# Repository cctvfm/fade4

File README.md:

# fade4
A performance MIDI and CV controller based on SAMD21G

Fade 4 runs on an Atmel SAMD21G microcontroller running the Feather M0 Bootloader. This allows Fade 4 to be developed on using the Arduino programming environment, and make use of Arduino libraries.

The SAMD21G handles all USB communication while using it's internal ADCs to read the positions of the faders. Each fader is connected between 0V and 3.3V, with the wiper providing a voltage between 0V and 3.3V. An opamp is used to multiply this voltage by 1.5x to provide 0 to 5V to the CV outputs. The fader position is sampled through Responsive Analog Read to smooth out any jumpiness in the measurement.

MIDI is handled using the Forty Seven Effects MIDI Library, making sending MIDI and USB MIDI the simplest part of this device.

The 7 segment LED displays are of the common cathode type, meaning the 7 LEDs in the character have their anodes broken out to individual pins, while the cathodes are grouped together into one pin. I use a 2N3904 transistor connected to this cathode pin to enable the digit, allowing the 4 digits to share character pins, as long as each has its own transistor and cathode pin. 

These displays need to be enabled one at a time, and using persistence of vision it appears that the 4 digits are on all the time. The timing of these characters is handled by TC3, triggering an interrupt to turn the current LED charactor off, reconfigure the pins, and turn the next one on.

A second timer, TC0, is used to generate a PWM signal on the 4 cathode transistor pins. This PWM signal can be changed to adjust the brightness of the display from 0 to 100%.

_FIRMWARE UPDATE_

1) Download the .UF2 file for the new firmware

2) Remove the 4 screws on the bottom of Fade 4, and remove the cover.

3) Plug Fade 4 into your computer using  a USB-C cable. Mac or Windows or Linux, doesn't matter. It will show up as a MIDI device named "Fade 4".

4) Double tap the button on the PCB marked "RESET". Two quick presses. A USB drive will appear on your computer, labelled "FEATHER" or "FEATHERBOOT"

5) Copy and paste the UF2 file into the USB drive. If prompted to overwrite, select YES.

6) Unplug, and reinstall the bottom cover. The firmware has been updated.

_HACKING_

You just need the .ino file in a folder named the same as it. Arduino or Arduino IDE, but you will need the following packages:

Adafruit SAMD Board Package
Flash Storage
Responsive Analog Read
MIDI

All firmware updates can be done over the USB C port. The 4 pin header is just for initial bootloader burn using an SWD programmer.

*November 2023:* 5 units built for testing. These are V1.0 units. They have an issue where the ADC is referenced to 5V and not 3.3V, so depending on USB power supply, the faders may not reach all the way to 127. fade4.ino.feather_m0-MAX975.uf2 provided as a fix for these units.

*April 15 2024:* Initial kit run. V1.1 released, fixes above issue. Build guide published to cctv.fm/fade4. Shipped with V1.1 preflashed.

*April 17 2023:* Bug fix, channels via TRS do not match channels via USB. Due to USB library counting channels from 0 and MIDI library counting from 1.

*May 8 2024:* Chris found a bug causing Program Changes to not function at all on V12, added bounds checking to message types.

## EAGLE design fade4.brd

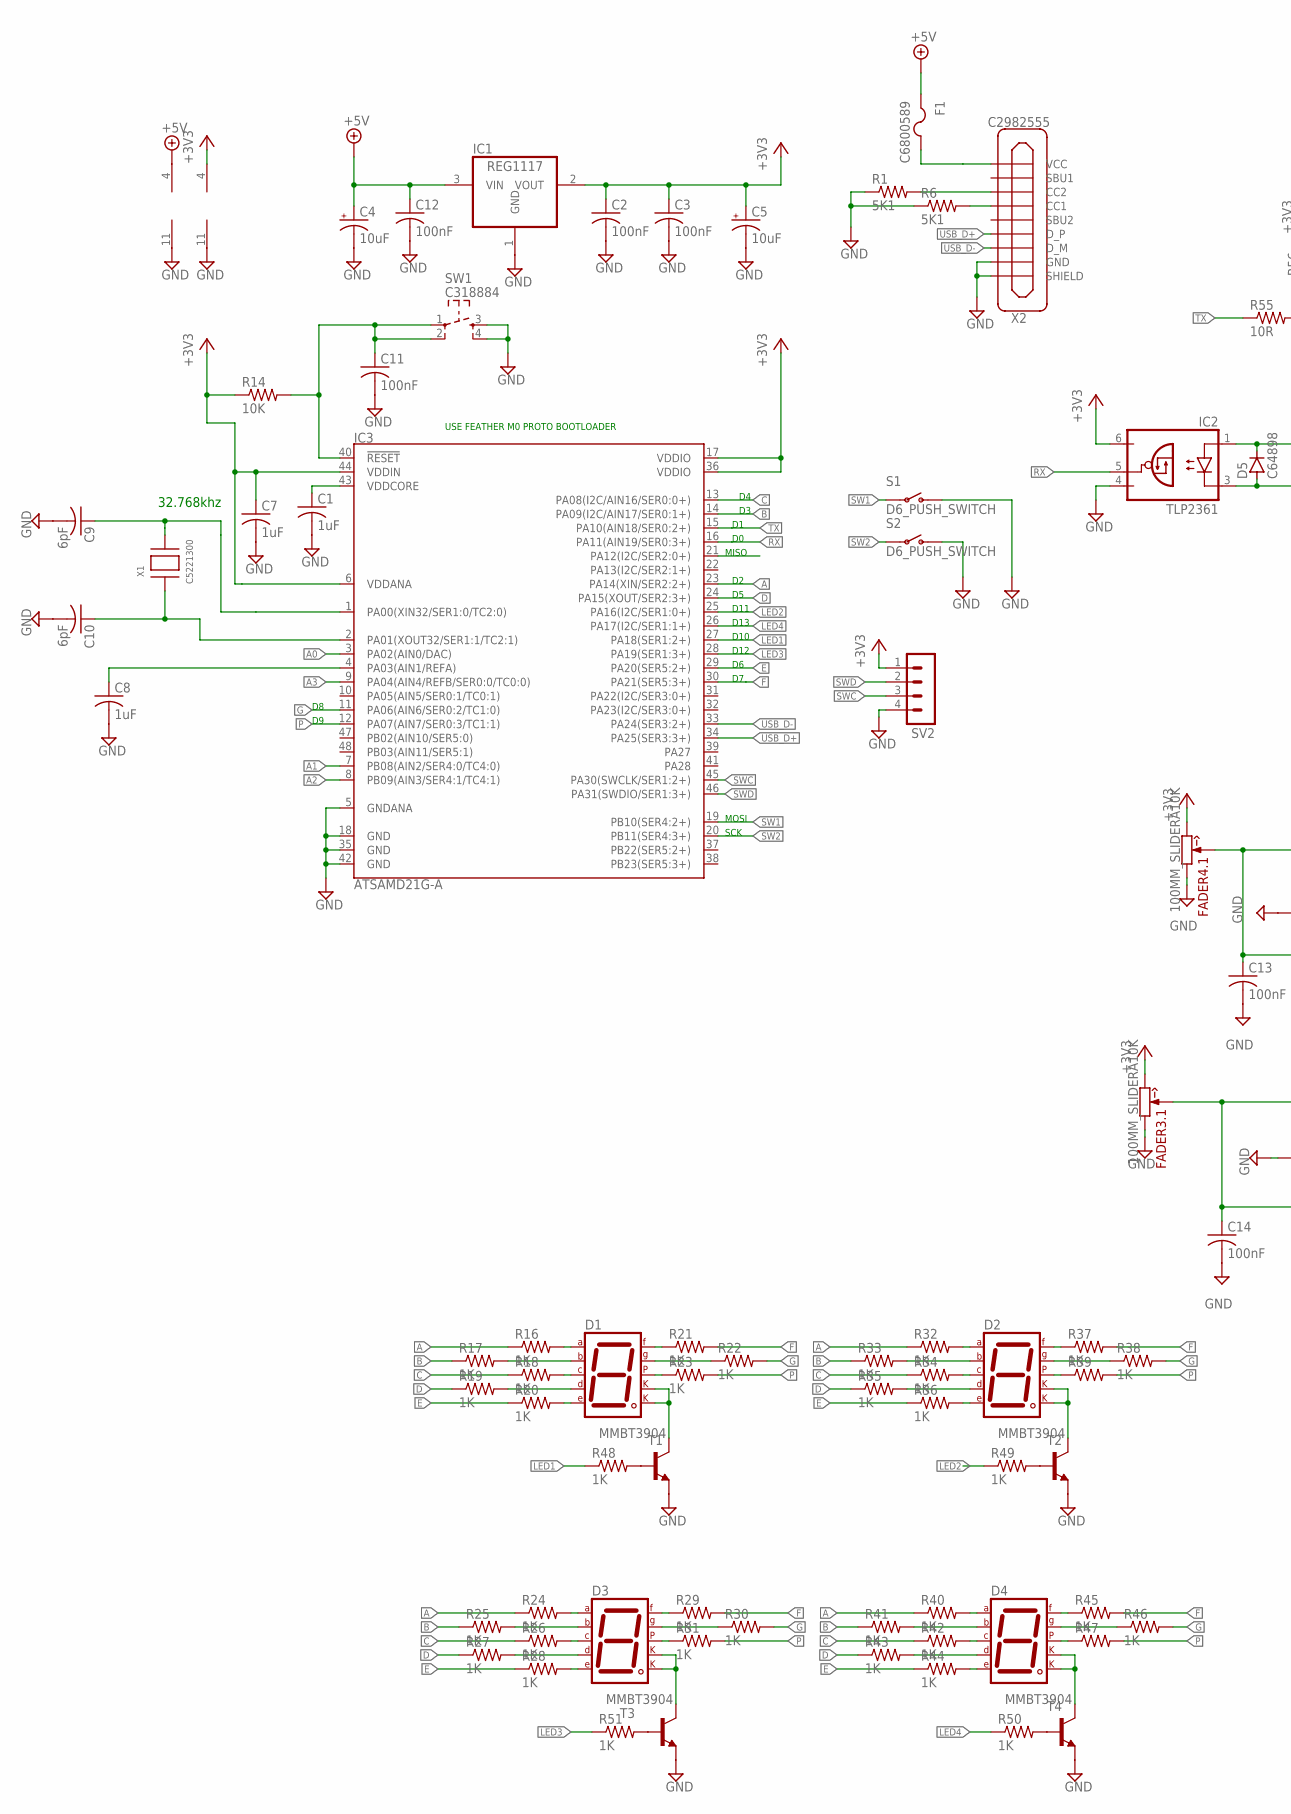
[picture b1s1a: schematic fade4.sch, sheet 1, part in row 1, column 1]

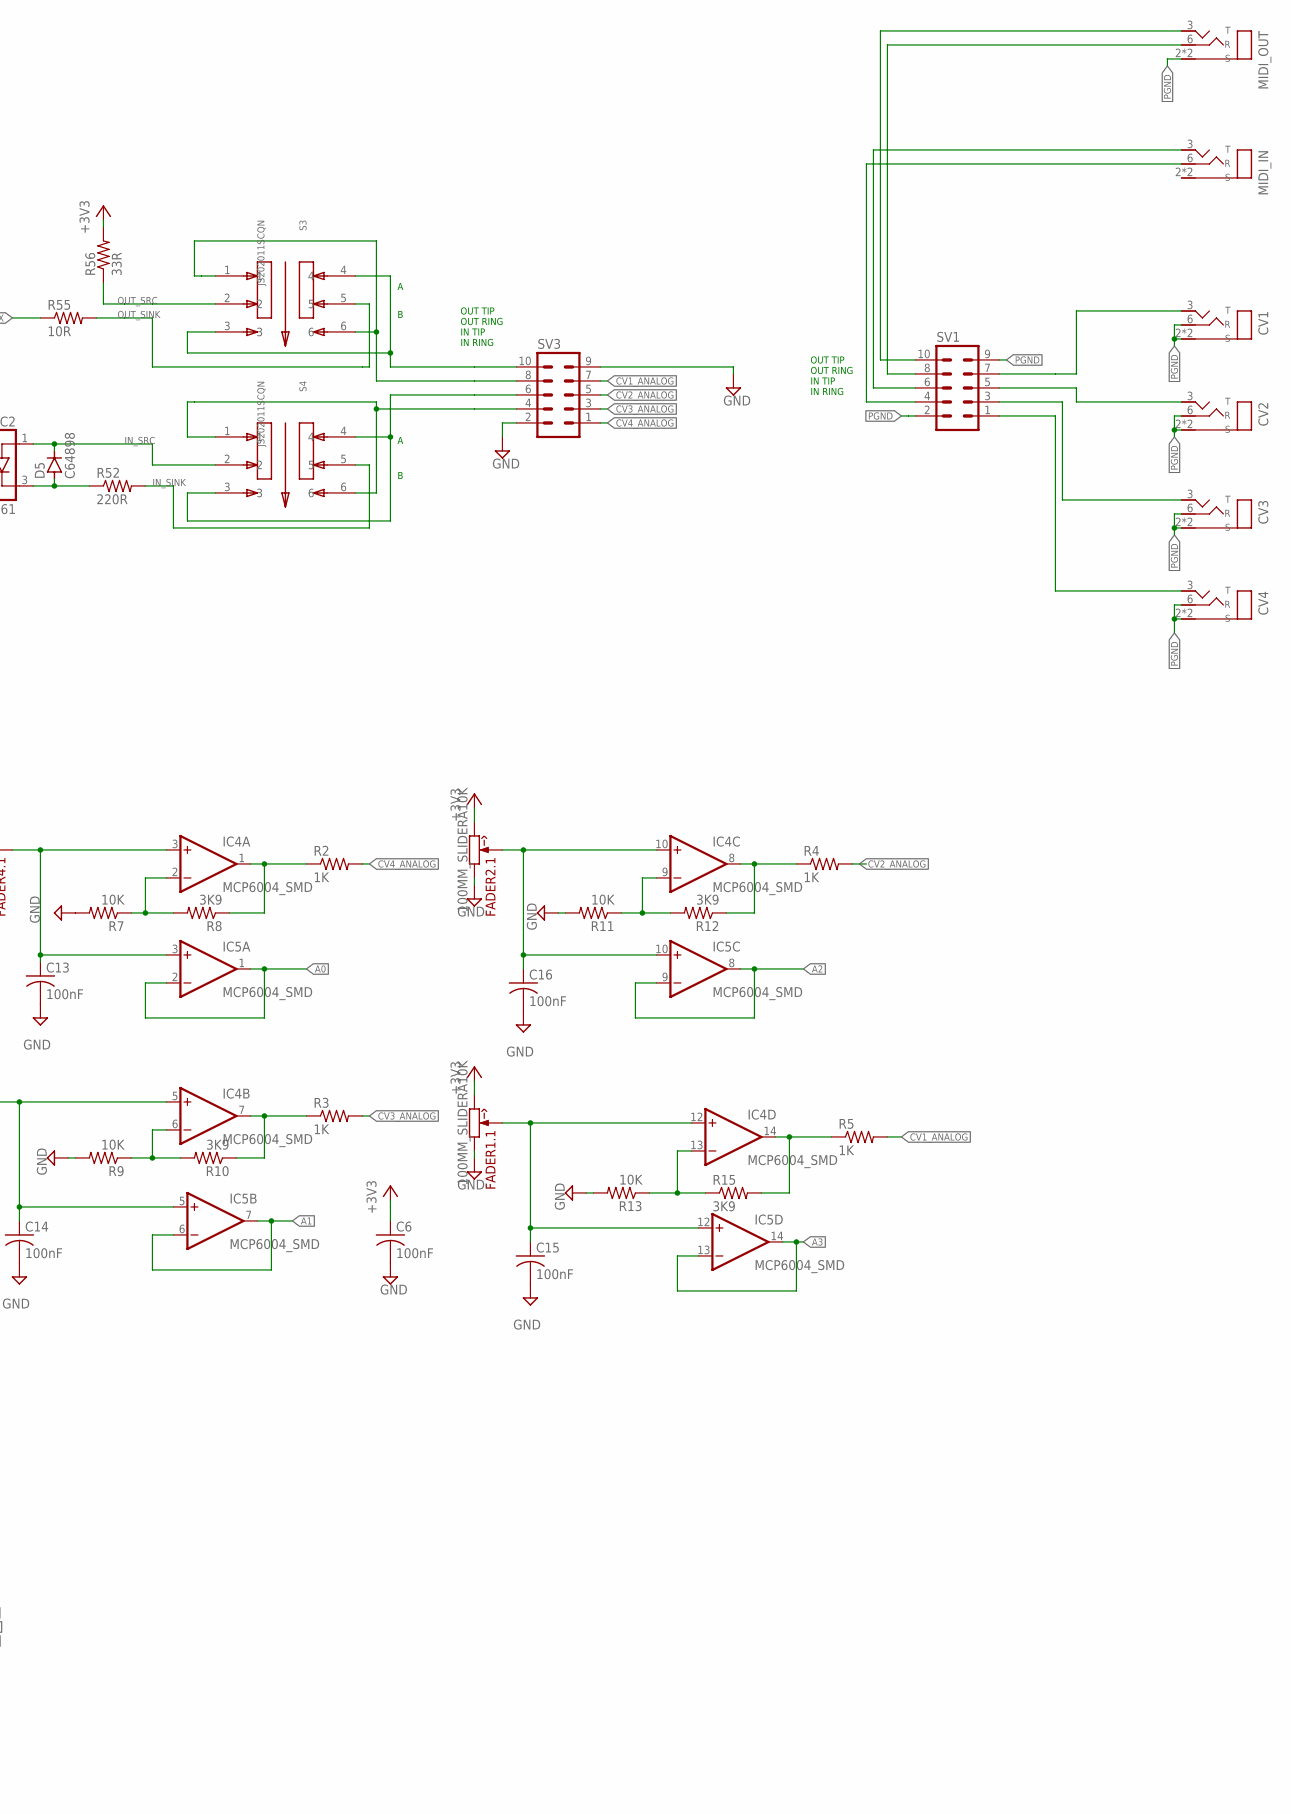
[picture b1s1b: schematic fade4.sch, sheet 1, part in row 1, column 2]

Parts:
C1, C7, C8: 1uF; C0603K
C2, C3, C6, C11, C12, C13, C14, C15, C16: 100nF; C0603K
C4, C5: 10uF; A/3216-18R
C9, C10: 6pF; C0603K
CV1, CV2, CV3, CV4: C725772
D1, D2, D3, D4: 7SEG-CK; 7SEG-13
D5: C64898; SOD123
F1: C6800589; R1206
FADER1, FADER2, FADER3, FADER4: 100MM_SLIDERA10K; 100MM-SLIDER
IC1: REG1117; SOT223
IC2: TLP2361; SOIC-5
IC3: ATSAMD21G-A; TQFP-48
IC4, IC5: MCP6004_SMD; SO14
MIDI_IN: C725772
MIDI_OUT: C725772
R1, R6: 5K1; R0603
R2, R3, R4, R5, R16, R17, R18, R19, R20, R21, R22, R23, R24, R25, R26, R27, R28, R29, R30, R31, R32, R33, R34, R35, R36, R37, R38, R39, R40, R41, R42, R43, R44, R45, R46, R47, R48, R49, R50, R51: 1K; R0603
R7, R9, R11, R13, R14: 10K; R0603
R8, R10, R12, R15: 3K9; R0603
R52: 220R; R0603
R55: 10R; R1206
R56: 33R; R1206
S1, S2: D6_PUSH_SWITCH
S3, S4: JS202011SCQN; SW_JS202011SCQN
SV1, SV3: MA05-2
SV2: MA04-1
SW1: C318884; SW_TACT_SMALL
T1, T2, T3, T4: MMBT3904; SOT23-BEC
X1: C5221300; XTAL3215
X2: C2982555

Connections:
+3V3: C2.1, C3.1, C5.+, C6.1, C7.1, FADER1.A3 (CW), FADER2.A3 (CW), FADER3.A3 (CW), FADER4.A3 (CW), IC1.2 (VOUT), IC2.6 (VCC), IC3.6 (VDDANA), IC3.17 (VDDIO), IC3.36 (VDDIO), IC3.44 (VDDIN), IC5.4 (V+), R14.1, R56.2, SV2.1
+5V: C4.+, C12.1, F1.1, IC1.3 (VIN), IC4.4 (V+)
A: IC3.23 (PA14(XIN/SER2:2+)), R16.1, R24.1, R32.1, R40.1
A0: IC3.3 (PA02(AIN0/DAC)), IC5.1 (OUT), IC5.2 (-IN)
A1: IC3.7 (PB08(AIN2/SER4:0/TC4:0)), IC5.6 (-IN), IC5.7 (OUT)
A2: IC3.8 (PB09(AIN3/SER4:1/TC4:1)), IC5.8 (OUT), IC5.9 (-IN)
A3: IC3.9 (PA04(AIN4/REFB/SER0:0/TC0:0)), IC5.13 (-IN), IC5.14 (OUT)
B: IC3.14 (PA09(I2C/AIN17/SER0:1+)), R17.1, R25.1, R33.1, R41.1
C: IC3.13 (PA08(I2C/AIN16/SER0:0+)), R18.1, R26.1, R34.1, R42.1
CV1_ANALOG: R5.2, SV3.7
CV2_ANALOG: R4.2, SV3.5
CV3_ANALOG: R3.2, SV3.3
CV4_ANALOG: R2.2, SV3.1
D: IC3.24 (PA15(XOUT/SER2:3+)), R19.1, R27.1, R35.1, R43.1
E: IC3.29 (PA20(SER5:2+)), R20.1, R28.1, R36.1, R44.1
F: IC3.30 (PA21(SER5:3+)), R21.2, R29.2, R37.2, R45.2
G: IC3.11 (PA06(AIN6/SER0:2/TC1:0)), R22.2, R30.2, R38.2, R46.2
GND: C1.2, C2.2, C3.2, C4.-, C5.-, C6.2, C7.2, C8.2, C9.2, C10.2, C11.2, C12.2, C13.2, C14.2, C15.2, C16.2, FADER1.A1 (CCW), FADER2.A1 (CCW), FADER3.A1 (CCW), FADER4.A1 (CCW), IC1.1 (GND), IC2.4 (GND), IC3.5 (GNDANA), IC3.18 (GND), IC3.35 (GND), IC3.42 (GND), IC4.11 (V-), IC5.11 (V-), R1.1, R6.1, R7.2, R9.2, R11.2, R13.2, S1.P$1 (O), S1.P$2 (O), S2.P$1 (O), S2.P$2 (O), SV2.4, SV3.2, SV3.9, SW1.3, SW1.4, T1.E, T2.E, T3.E, T4.E, X2.A12B1 (GND), X2.B12A1 (GND), X2.SHIELD1 (SHIELD), X2.SHIELD2 (SHIELD), X2.SHIELD3 (SHIELD), X2.SHIELD4 (SHIELD)
IN_RING: S4.1, S4.6, SV3.4
IN_SINK: R52.2, S4.5
IN_SRC: D5.1 (C), IC2.1 (A), S4.2
IN_TIP: S4.3, S4.4, SV3.6
LED1: IC3.27 (PA18(SER1:2+)), R48.1
LED2: IC3.25 (PA16(I2C/SER1:0+)), R49.1
LED3: IC3.28 (PA19(SER1:3+)), R51.1
LED4: IC3.26 (PA17(I2C/SER1:1+)), R50.1
unnamed: R6.2, X2.A5 (CC1)
unnamed: R1.2, X2.B5 (CC2)
unnamed: C1.1, IC3.43 (VDDCORE)
unnamed: F1.2, X2.A9B4 (VCC), X2.B9A4 (VCC)
unnamed: C13.1, FADER4.A2 (W), IC4.3 (+IN), IC5.3 (+IN)
unnamed: C14.1, FADER3.A2 (W), IC4.5 (+IN), IC5.5 (+IN)
unnamed: C16.1, FADER2.A2 (W), IC4.10 (+IN), IC5.10 (+IN)
unnamed: C15.1, FADER1.A2 (W), IC4.12 (+IN), IC5.12 (+IN)
unnamed: IC4.1 (OUT), R2.1, R8.1
unnamed: IC4.7 (OUT), R3.1, R10.1
unnamed: IC4.8 (OUT), R4.1, R12.1
unnamed: IC4.14 (OUT), R5.1, R15.2
unnamed: D1.7 (A), R16.2
unnamed: IC4.9 (-IN), R11.1, R12.2
unnamed: D1.6 (B), R17.2
unnamed: IC4.13 (-IN), R13.1, R15.1
unnamed: CV1.3 (T), SV1.7
unnamed: IC4.6 (-IN), R9.1, R10.2
unnamed: D1.4 (C), R18.2
unnamed: D1.2 (D), R19.2
unnamed: D1.1 (E), R20.2
unnamed: D3.7 (A), R24.2
unnamed: D3.6 (B), R25.2
unnamed: D3.4 (C), R26.2
unnamed: D3.2 (D), R27.2
unnamed: D1.9 (F), R21.1
unnamed: D1.10 (G), R22.1
unnamed: D1.5 (DP), R23.1
unnamed: D5.2 (A), IC2.3 (C), R52.1
unnamed: D3.1 (E), R28.2
unnamed: D3.9 (F), R29.1
unnamed: D3.10 (G), R30.1
unnamed: D3.5 (DP), R31.1
unnamed: D2.7 (A), R32.2
unnamed: D2.6 (B), R33.2
unnamed: D2.4 (C), R34.2
unnamed: D2.2 (D), R35.2
unnamed: D2.1 (E), R36.2
unnamed: D2.9 (F), R37.1
unnamed: C8.1, IC3.4 (PA03(AIN1/REFA))
unnamed: C9.1, IC3.1 (PA00(XIN32/SER1:0/TC2:0)), X1.P$2
unnamed: C10.1, IC3.2 (PA01(XOUT32/SER1:1/TC2:1)), X1.P$1
unnamed: D2.10 (G), R38.1
unnamed: D2.5 (DP), R39.1
unnamed: D4.7 (A), R40.2
unnamed: D4.6 (B), R41.2
unnamed: D4.4 (C), R42.2
unnamed: D4.2 (D), R43.2
unnamed: D4.1 (E), R44.2
unnamed: D4.9 (F), R45.1
unnamed: D4.10 (G), R46.1
unnamed: D4.5 (DP), R47.1
unnamed: CV2.3 (T), SV1.5
unnamed: CV3.3 (T), SV1.3
unnamed: CV4.3 (T), SV1.1
unnamed: MIDI_OUT.3 (T), SV1.10
unnamed: MIDI_OUT.6 (R), SV1.8
unnamed: MIDI_IN.3 (T), SV1.6
unnamed: MIDI_IN.6 (R), SV1.4
unnamed: R48.2, T1.B
unnamed: R49.2, T2.B
unnamed: R50.2, T4.B
unnamed: R51.2, T3.B
unnamed: IC4.2 (-IN), R7.1, R8.2
unnamed: D3.3 (CK1), D3.8 (CK2), T3.C
unnamed: D4.3 (CK1), D4.8 (CK2), T4.C
unnamed: D2.3 (CK1), D2.8 (CK2), T2.C
unnamed: D1.3 (CK1), D1.8 (CK2), T1.C
OUT_RING: S3.1, S3.6, SV3.8
OUT_SINK: R55.2, S3.5
OUT_SRC: R56.1, S3.2
OUT_TIP: S3.3, S3.4, SV3.10
P: IC3.12 (PA07(AIN7/SER0:3/TC1:1)), R23.2, R31.2, R39.2, R47.2
PGND: CV1.2 (S), CV1.5 (S), CV1.6 (R), CV2.2 (S), CV2.5 (S), CV2.6 (R), CV3.2 (S), CV3.5 (S), CV3.6 (R), CV4.2 (S), CV4.5 (S), CV4.6 (R), MIDI_OUT.2 (S), MIDI_OUT.5 (S), SV1.2, SV1.9
RST_PCB: C11.1, IC3.40 (!RESET!), R14.2, SW1.1, SW1.2
RX: IC2.5 (VO), IC3.16 (PA11(AIN19/SER0:3+))
SW1: IC3.19 (PB10(SER4:2+)), S1.P$3, S1.P$4
SW2: IC3.20 (PB11(SER4:3+)), S2.P$3, S2.P$4
SWC: IC3.45 (PA30(SWCLK/SER1:2+)), SV2.3
SWD: IC3.46 (PA31(SWDIO/SER1:3+)), SV2.2
TX: IC3.15 (PA10(AIN18/SER0:2+)), R55.1
USB_D+: IC3.34 (PA25(SER3:3+)), X2.A6 (D_P), X2.B6 (D_P)
USB_D-: IC3.33 (PA24(SER3:2+)), X2.A7 (D_M), X2.B7 (D_M)

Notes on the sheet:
32.768khz
USE FEATHER M0 PROTO BOOTLOADER
D10
D11
D12
D13
MOSI
SCK
MISO
OUT TIP OUT RING IN TIP IN RING

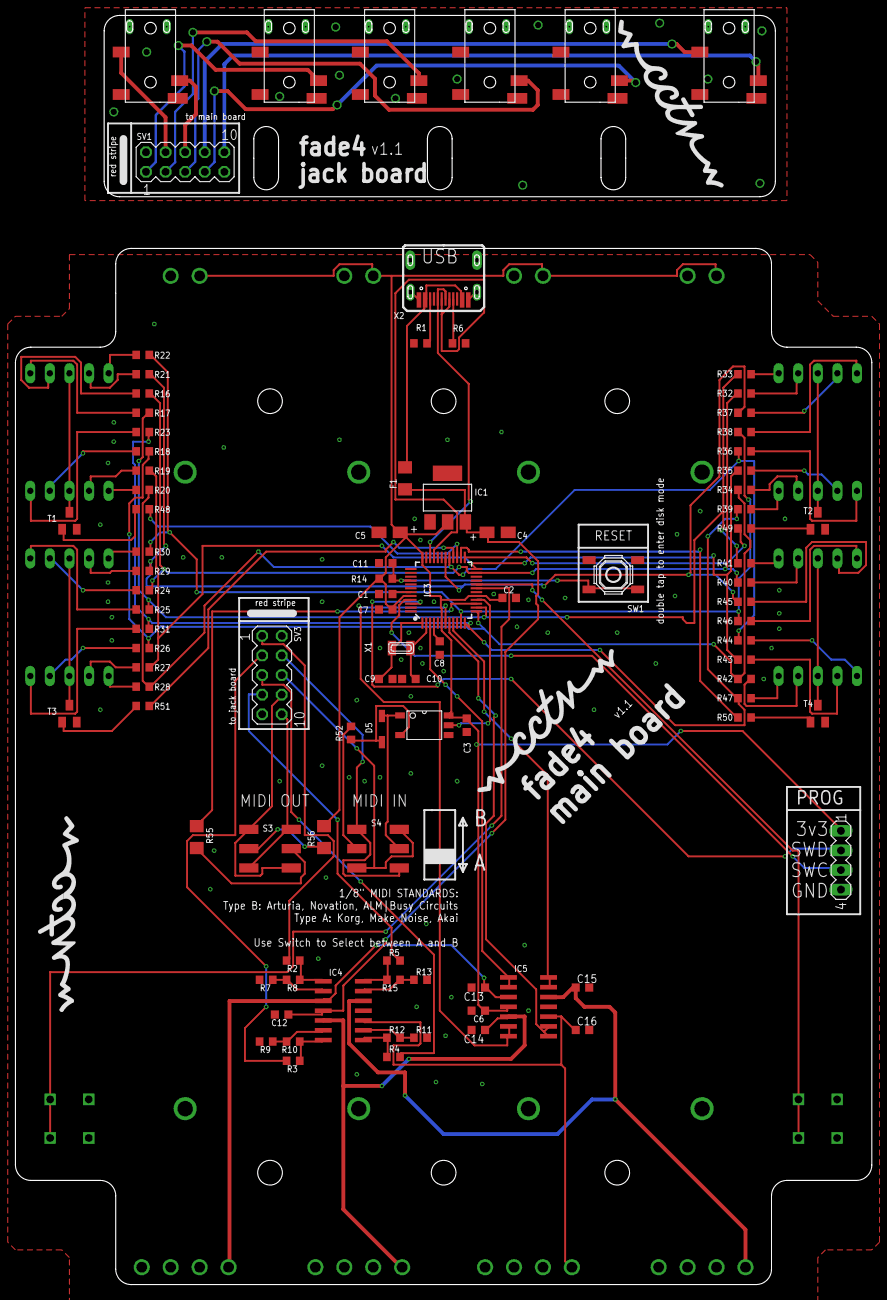
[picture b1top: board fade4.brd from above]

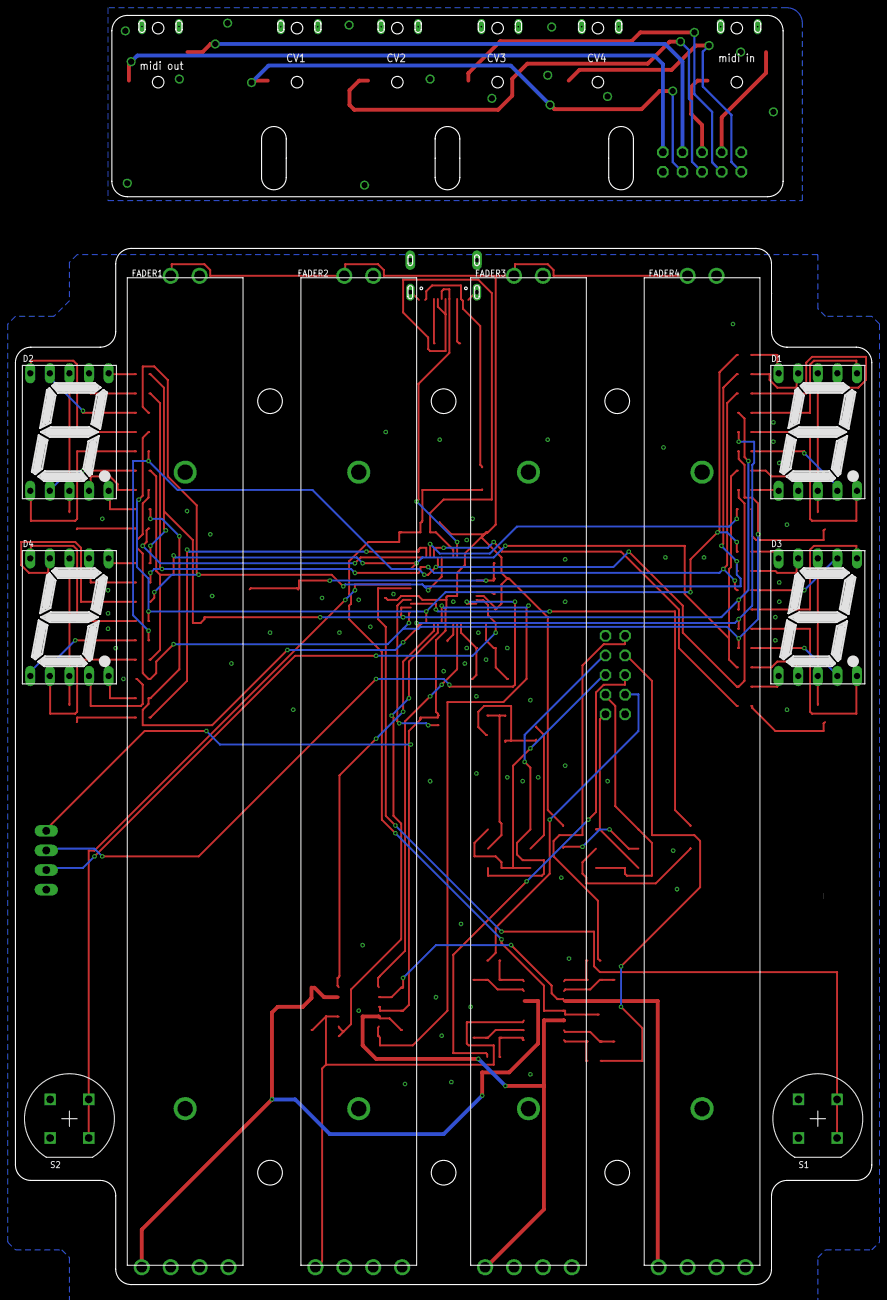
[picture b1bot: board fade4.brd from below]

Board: 2 copper layers, 111.0 x 164.5 mm, 105 parts (10 on the bottom side), 109 nets.

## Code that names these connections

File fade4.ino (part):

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#define POT2 A2
#define POT1 A3

#define DIGIT1 11 //PA16  TCC0/WO[6] F
#define DIGIT2 10 //PA18  TCC0/WO[2] F
#define DIGIT3 13 //PA17  TCC0/WO[7] F
#define DIGIT4 12 //PA19  TCC0/WO[3] F

#define SW2 MOSI
#define SW1 SCK
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  PORT->Group[g_APinDescription[DIGIT4].ulPort].PINCFG[g_APinDescription[DIGIT4].ulPin].bit.PMUXEN = 1;
  
  //assign the 4 outputs to the PWM registers on PMUX
  PORT->Group[g_APinDescription[DIGIT1].ulPort].PMUX[g_APinDescription[DIGIT1].ulPin >> 1].reg |= PORT_PMUX_PMUXE_F;  // digit1 is on PA16 = even     
  PORT->Group[g_APinDescription[DIGIT2].ulPort].PMUX[g_APinDescription[DIGIT2].ulPin >> 1].reg |= PORT_PMUX_PMUXE_F; // 2 is on PA18 = even 
  PORT->Group[g_APinDescription[DIGIT3].ulPort].PMUX[g_APinDescription[DIGIT3].ulPin >> 1].reg |= PORT_PMUX_PMUXO_F;  // 3 is on PA17 = odd
  PORT->Group[g_APinDescription[DIGIT4].ulPort].PMUX[g_APinDescription[DIGIT4].ulPin >> 1].reg |= PORT_PMUX_PMUXO_F; // 4 is on PA19 = odd

  //set drive str for all 4

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
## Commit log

2024-04-16 Initial upload V1.1
2024-04-16 wrote README.md
2024-04-18 Bug fix
2024-04-18 Fixed MIDI issue on V1 boards
    Reported issue that messages are over 127 when used with a hot USB power supply. Added hard limit to 127.
2024-04-18 Uploaded v13 fixing MIDI out of range issues
2024-05-08 Fixed issue with Program Changes not functioning
    Issue with going out of bounds when setting PC as the message. Fixed with bounds checking.
2024-05-08 Update README.md for V13

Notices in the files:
fade4.ino:
// TCC1 CC0 - on D11 50% pin 1
REG_TCC0_CC3 = 50; // TCC1 CC0 - on D11 50% pin 3
parts and their libraries:
SparkFun-IC-Microcontroller: Licensing: Creative Commons ShareAlike 4.0 International - https://creativecommons.org/licenses/by-sa/4.0
